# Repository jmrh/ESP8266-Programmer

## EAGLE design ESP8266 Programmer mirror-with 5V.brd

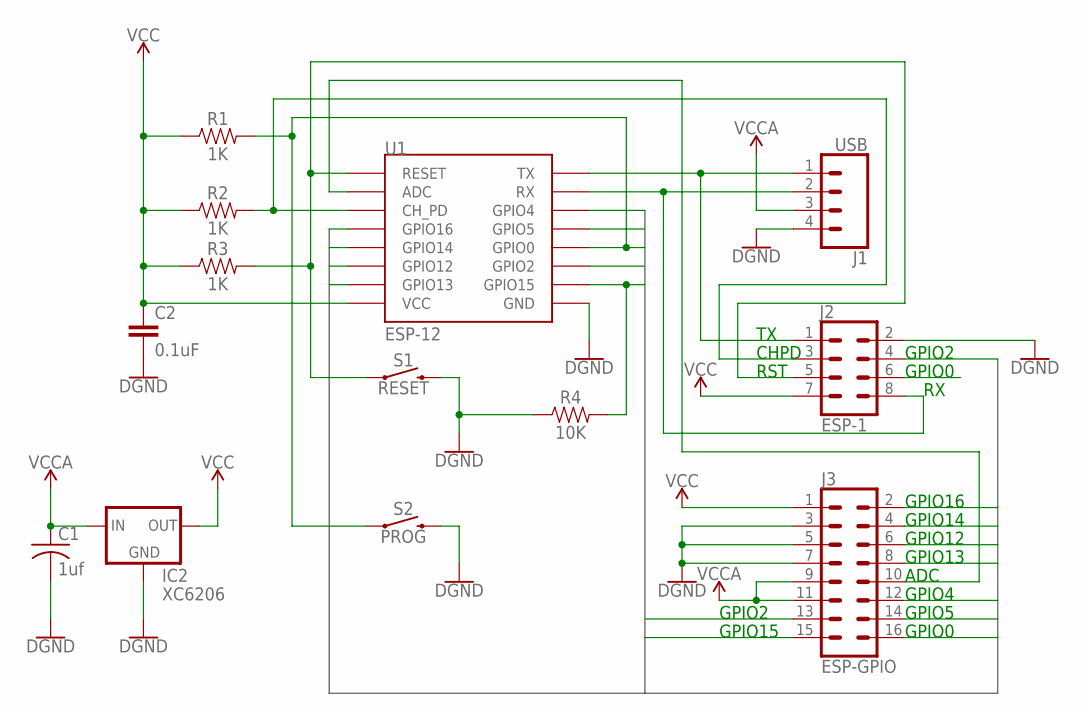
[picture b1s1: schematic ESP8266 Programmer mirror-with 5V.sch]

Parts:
C1: 1uf; C025-040X050
C2: 0.1uF; CAP-PTH-10MM
IC2: XC6206; SOT89R
J1: USB; 1X04
J2: ESP-1; 2X4
J3: ESP-GPIO; 2X8
R1, R2, R3: 1K; AXIAL-0.3-KIT
R4: 10K; AXIAL-0.3-KIT
S1: RESET; TACTILE_SWITCH_PTH_6.0MM
S2: PROG; TACTILE_SWITCH_PTH_6.0MM
U1: ESP-12; ESP12

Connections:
GND: C1.2, C2.2, IC2.1 (GND), J1.4, J2.2, J3.3, J3.5, J3.7, R4.P$1 (1), S1.3 (2), S2.3 (2), U1.GND
GPIO0: J2.6, J3.16, R1.P$2 (2), S2.1, U1.GPIO0
GPIO2: J2.4, J3.13, U1.GPIO2
GPIO4: J3.12, U1.GPIO4
GPIO5: J3.14, U1.GPIO5
GPIO12: J3.6, U1.GPIO12
GPIO13: J3.8, U1.GPIO13
GPIO14: J3.4, U1.GPIO14
GPIO15: J3.15, R4.P$2 (2), U1.GPIO15
GPIO16: J3.2, U1.GPIO16
unnamed: J2.5, R3.P$2 (2), S1.1, U1.RESET
unnamed: J2.3, R2.P$2 (2), U1.CH_PD
unnamed: J1.1, J2.1, U1.TX
unnamed: J1.2, J2.8, U1.RX
unnamed: J3.10, U1.ADC
VCC: C2.1, IC2.2 (OUT), J2.7, J3.1, R1.P$1 (1), R2.P$1 (1), R3.P$1 (1), U1.VCC
VCCA: C1.1, IC2.3 (IN), IC2.4 (IN), J1.3, J3.9, J3.11

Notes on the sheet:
GPIO2
GPIO15
GPIO16
GPIO14
GPIO12
GPIO13
GPIO4
GPIO5
GPIO0
ADC
CHPD
RST

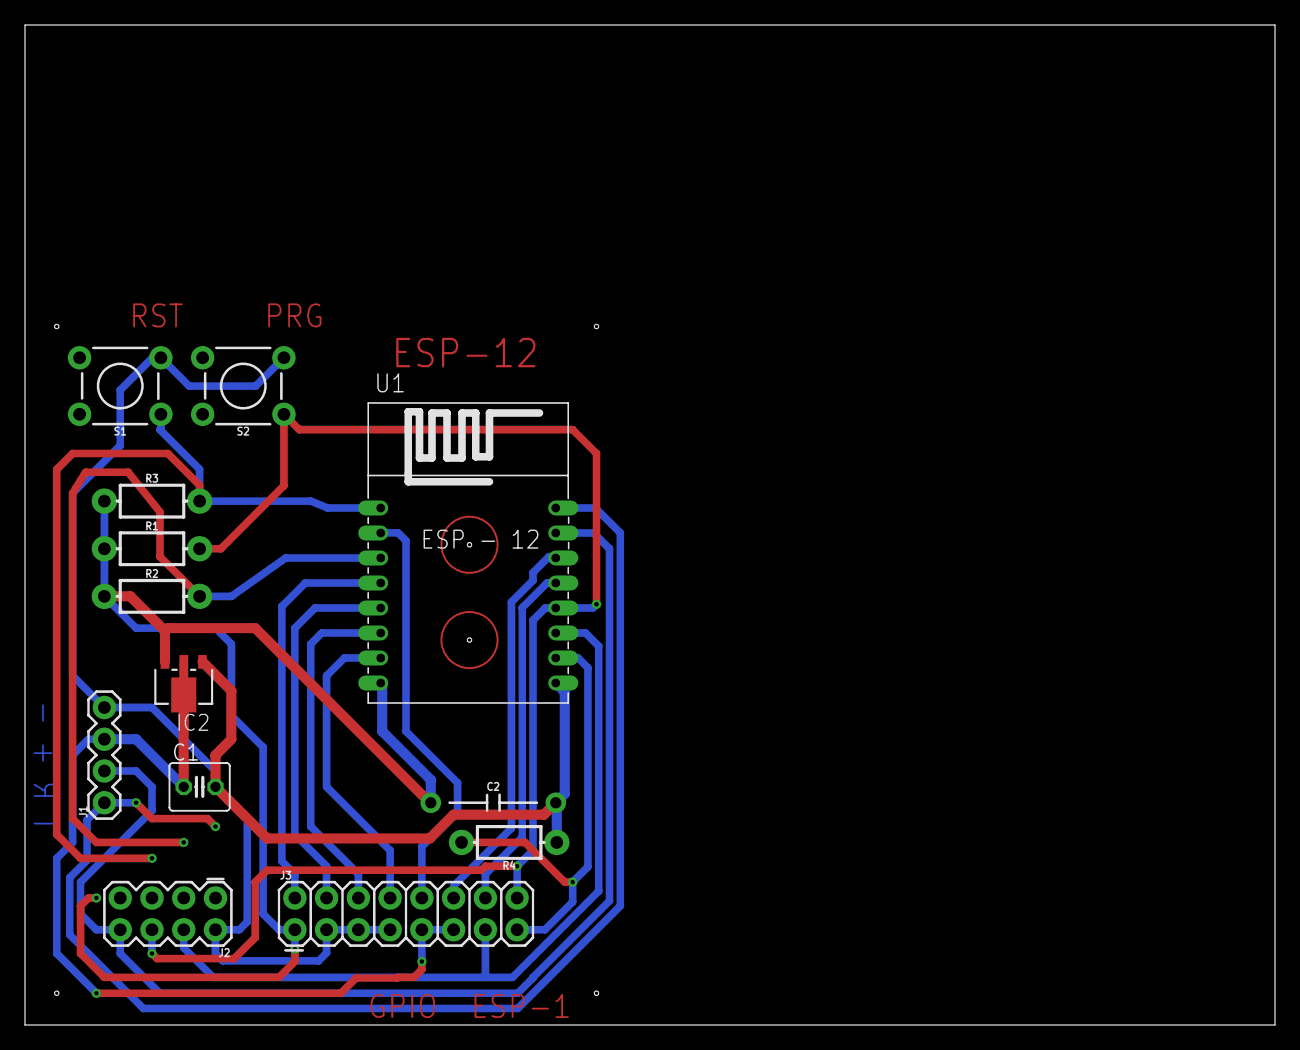
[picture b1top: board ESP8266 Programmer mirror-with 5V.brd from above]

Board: 2 copper layers, 100.0 x 80.0 mm, 13 parts (0 on the bottom side), 17 nets.

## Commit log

2020-05-26 Add files via upload
    added new version of the Eagle CAD schematic and board for the ESP8266 programmer with the 5 V available in the header.
2020-05-26 Add files via upload
    ESP8266 Schematic screenshot
2020-05-26 Add files via upload
    Programmer Board screenshot.

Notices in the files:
parts and their libraries:
SparkFun-Connectors: Licensing: Creative Commons ShareAlike 4.0 International - https://creativecommons.org/licenses/by-sa/4.0
